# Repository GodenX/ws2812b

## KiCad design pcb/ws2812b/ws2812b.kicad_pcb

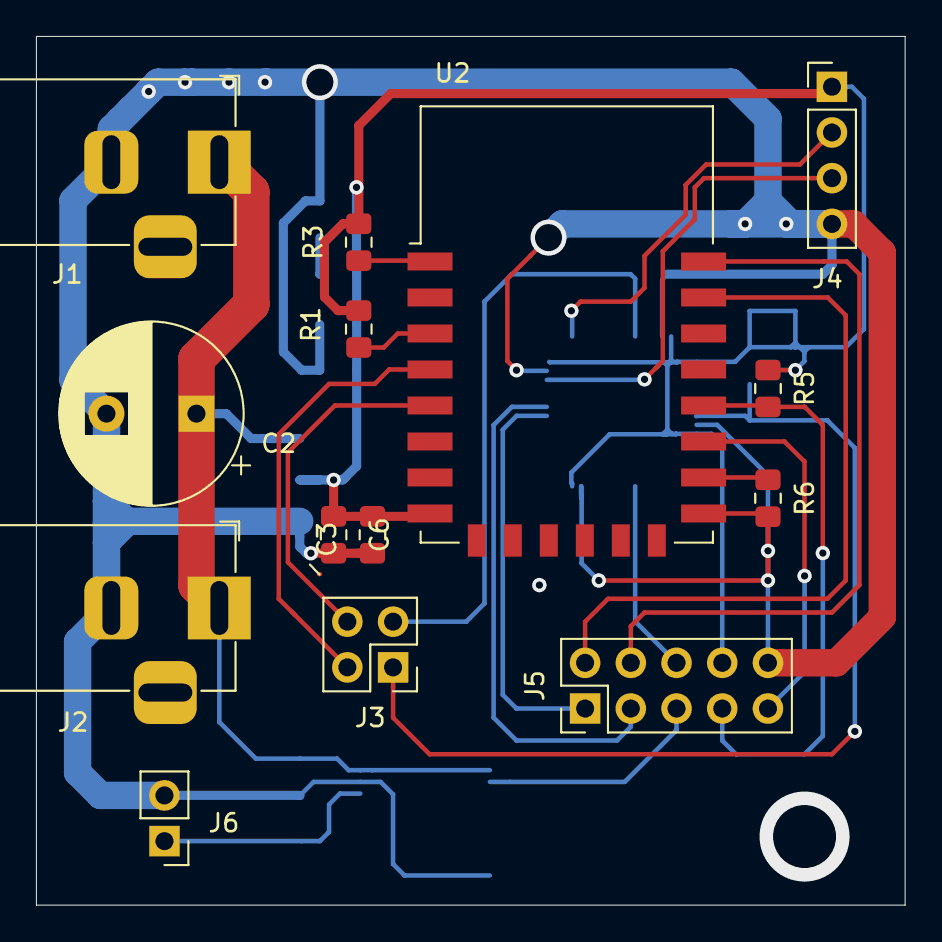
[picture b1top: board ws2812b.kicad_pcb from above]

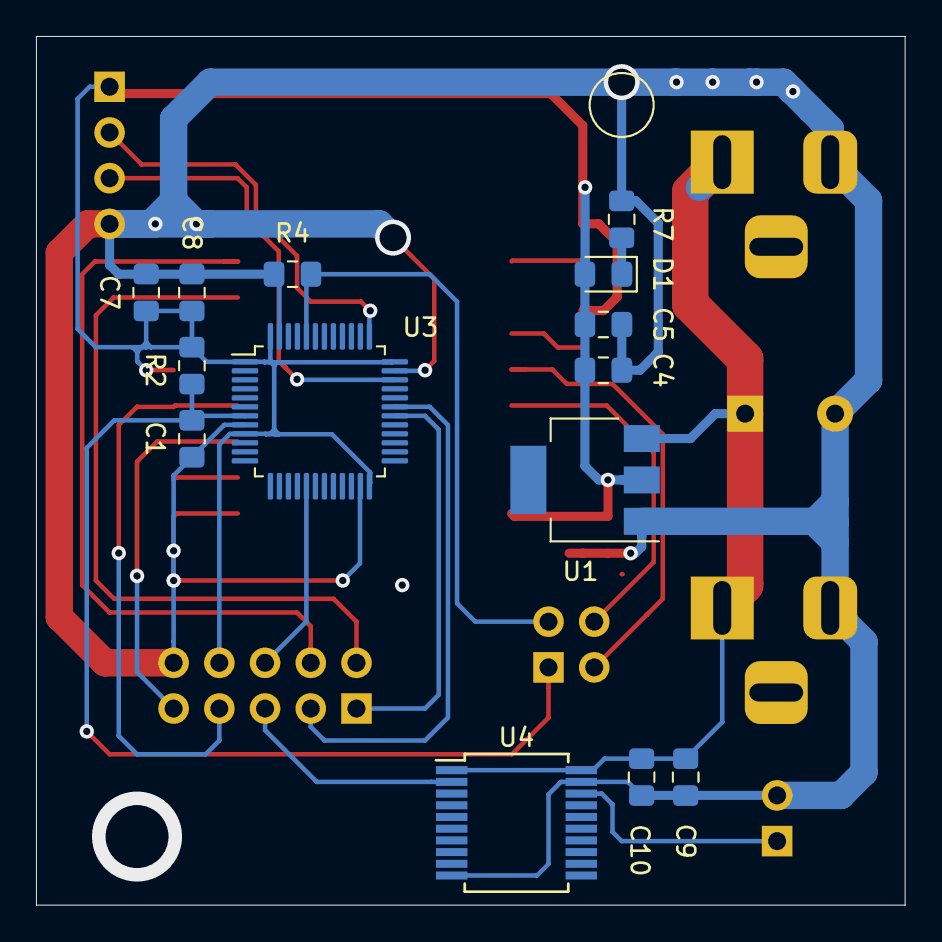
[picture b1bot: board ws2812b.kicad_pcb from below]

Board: 2 copper layers, 48.3 x 48.3 mm, 28 parts (14 on the bottom side), 22 nets.

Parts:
C1, C6, C8, C10: 0.1uF; C_0805_2012Metric_Pad1.15x1.40mm_HandSolder
C2: 470uF; CP_Radial_D10.0mm_P5.00mm
C3, C4, C7, C9: 10uF; C_0805_2012Metric_Pad1.15x1.40mm_HandSolder
C5: 0.1uf; C_0805_2012Metric_Pad1.15x1.40mm_HandSolder
D1: LED; LED_0805_2012Metric_Pad1.15x1.40mm_HandSolder
J1, J2: Jack-DC; BarrelJack_Horizontal
J3: Conn_02x02_Top_Bottom; PinHeader_2x02_P2.54mm_Vertical
J4: Conn_01x04; PinHeader_1x04_P2.54mm_Vertical
J5: Conn_02x05_Top_Bottom; PinHeader_2x05_P2.54mm_Vertical
J6: Conn_01x02; PinHeader_1x02_P2.54mm_Vertical
R1, R3, R4, R5, R6, R7: 10k; R_0805_2012Metric_Pad1.15x1.40mm_HandSolder
R2: 10K; R_0805_2012Metric_Pad1.15x1.40mm_HandSolder
U1: AMS1117-3.3; SOT-223
U2: ESP-12F; ESP-12E
U3: STM32F103C8Tx; LQFP-48_7x7mm_P0.5mm
U4: 74HC245; SSOP-20_5.3x7.2mm_P0.65mm

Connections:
0: C1.2, C2.2, C3.2, C4.2, C5.2, C6.2, C7.2, C8.2, C9.2, C10.2, J1.2, J2.2, J4.4, J5.10, J6.2, R4.2, R6.2, R7.2, U1.1, U2.15, U3.8, U3.23, U3.35, U3.47, U4.10, U4.19
+3V3: C3.1, C4.1, C5.1, C6.1, C7.1, C8.1, D1.2, J4.1, J5.8, R1.1, R2.1, R3.1, R5.1, U1.2, U2.8, U3.1, U3.9, U3.24, U3.36, U3.48
+5V: C2.1, C9.1, C10.1, J1.1, J2.1, U1.3, U4.1, U4.20
/BOOT0: J3.3, R4.1, U3.44
/DATA_IN: J5.6, U3.17
/DATA_OUT: J5.5, U4.2
/GPIO0: J5.7, R5.2, U2.18
/GPIO2: J5.9, U2.17
/GPIO14: J3.4, U2.5
/GPIO16: J3.2, U2.4
/NRST: C1.1, J3.1, R2.2, U3.7
/RXD: J5.2, U2.21
/SWCLK: J4.2, U3.37
/SWDIO: J4.3, U3.34
/TXD: J5.4, U2.22
/USART1_RX: J5.3, U3.31
/USART1_TX: J5.1, U3.30
unnamed: D1.1, R7.1
unnamed: J6.1, U4.18
unnamed: R1.2, U2.3
unnamed: R3.2, U2.1
unnamed: R6.1, U2.16

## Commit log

2019-04-22 first commit.
2019-04-25 20190425
2019-04-25 Generate gerber files.
